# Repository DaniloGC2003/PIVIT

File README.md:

# PIVIT
Este repositório faz parte de um PIVIT, ofertado pela Universidade Tecnológica Federal do Paraná.

## Requisitos
A fim de poder rodar os programas aqui desenvolvidos, será necessário:
- Instalar a IDE do Arduino;
- Instalar dependências das placas da Espressif. Na IDE, acessar File -> Preferences. Em seguida, colar a seguinte URL em "Additional boards manager URLs":
> https://raw.githubusercontent.com/espressif/arduino-esp32/gh-pages/package_esp32_index.json

Após esse processo, as dependências necessárias para a ESP-32 usada no projeto (incluindo a biblioteca de BLE) serão instaladas.
- Instalar o boards manager da ESP32. Em Tools -> Boards -> Boards Manager, pesquisar por "esp32". Em seguida, selecionar o board ESP32S3 Dev Module.

## Topologia
A solução envolve uma rede de dispositivos que usam BLE, ESP-NOW e barramentos seriais para realizar a comunicação entre si.

Esse projeto tem como objetivo criar um teste de tempo de reação. Nele, diversos dispositivos contendo um botão e um LED serão dispostos ao alcance do usuário. Sempre que um LED é aceso, o objetivo do usuário é apertar o botão desse dispositivo o mais rápido o possível. O intervalo de tempo entre o acender do LED e a resposta do usuário é chamado de tempo de reação. Essas informações serão enviadas a um aplicativo celular.

O dispositivo mestre é a ponte de comunicação entre os dispositivos com botão e LED (chamados slaves). Ele é composto por duas ESPs: a primeira realiza transmissão de dados BLE, já a outra realiza transmissão via ESP-NOW. As ESPs do dispositivo mestre usam barramentos seriais para comunicação entre si.

Os dispositivos slaves são ESPs que se comunicam com o dispositivo mestre via ESP-NOW. Possuem a função de enviar e receber informações do dispositivo mestre e cronometrar o tempo de reação do usuário.

A interface de contato do usuário com o dispositivo master pode operar em dois modos: 
- Push button: variável operation_mode =  1. Nesse caso, a interface de contato com o usuário é apenas um push button. Mais especificamente, o dispositivo entende como interação do usuário o curto do GPIO0 com GND.
- Sensor de pressão: variável operation_mode = 0. Nesse caso, o sensor BMP280 é conectado à ESP32. O sensor medirá a pressão de uma bolsa de ar, que servirá de ponto de contato com o usuário.

Por fim, o dispositivo móvel completa a topologia da solução. O aplicativo contido nele se comunica com o mestre via BLE e é responsável por enviar ordens de ativação de slaves.

## Pasta app
Contém arquivos referentes ao aplicativo android desenvolvido. O arquivo de extensão .apk é usado para instalar o app no dispositivo móvel. O arquivo de extensão .aia é usado para realizar edições na plataforma MIT app inventor.

## Pasta ESP-NOW
Diretório que contém códigos referentes ao atual desenvolvimento da solução. A solução envolve o uso de BLE e ESP-NOW.

### master.ino
Módulo legado. Código referente ao dispositivo central da solução. Possui interface bluetooth low energy (BLE) para comunicação com o celular e interface ESP-NOW para comunicação com dispostivos slave. O dispositivo mestre age como ponte entre o usuário e os dispositivos slave.

### master_BLE_Sensor.ino
Módulo referente à interface de comunicação BLE do dispositivo mestre. Comunica-se via BLE com o celular e via UART com o mestre ESP_NOW.

### master_ESPNOW.ino
Módulo referente à interface de comunicação ESP-NOW do dispositivo mestre. Comunica-se via ESP_NOW com os dispositivos slave e via UART com o mestre BLE.

### slave.ino
Código referente aos dispositivos secundários da solução. Possui interface ESP-NOW para comunicação com o dispositivo mestre.

### utils.h
Arquivo header que contém macros e estruturas de dados usadas pelo master e pelos slaves.

### Demais pastas
Códigos auxiliares e exemplos de implementações do protocolo ESP-NOW.

## backlog.txt
Arquivo de texto contendo tarefas/implementações que devem ser discutidas no futuro.

## Pasta kicad
Contém o projeto de PCIs para os dispositivos slave.

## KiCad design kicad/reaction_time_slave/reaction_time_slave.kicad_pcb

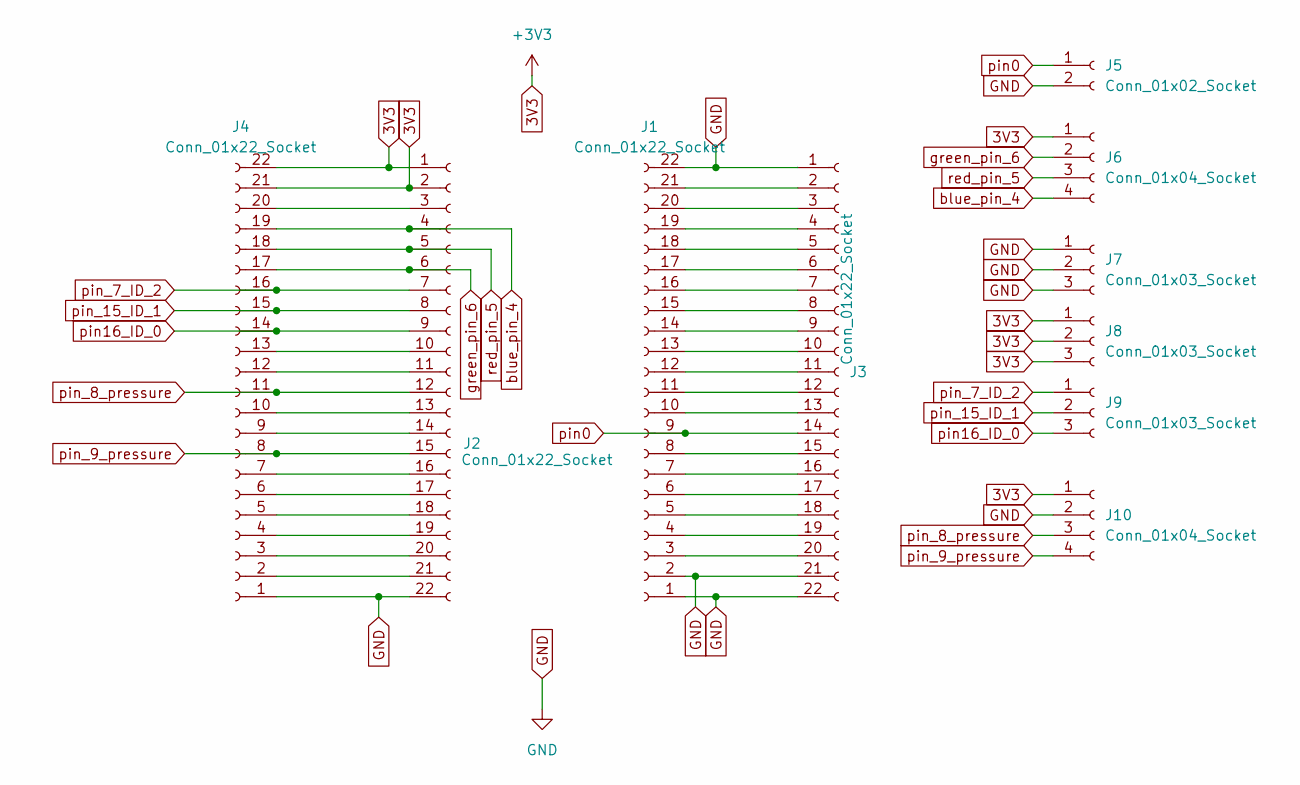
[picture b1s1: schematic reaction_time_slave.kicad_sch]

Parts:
J1, J2: Conn_01x22_Socket; PinSocket_1x22_P2.54mm_Vertical
J3, J4: Conn_01x22_Socket; PinHeader_1x22_P2.54mm_Vertical
J5: Conn_01x02_Socket; TerminalBlock_Phoenix_MKDS-1,5-2-5.08_1x02_P5.08mm_Horizont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
J6, J10: Conn_01x04_Socket; TerminalBlock_Phoenix_MKDS-1,5-4-5.08_1x04_P5.08mm_Horizont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
J7, J8, J9: Conn_01x03_Socket; PinHeader_1x03_P2.54mm_Vertical

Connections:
3V3: J2.1, J2.2, J4.21, J4.22, J6.1, J8.1, J8.2, J8.3, J10.1
GND: J1.1, J1.2, J1.22, J2.22, J3.1, J3.21, J3.22, J4.1, J5.2, J7.1, J7.2, J7.3, J10.2
unnamed: J1.3, J3.20
unnamed: J1.4, J3.19
unnamed: J1.5, J3.18
unnamed: J1.6, J3.17
unnamed: J1.7, J3.16
unnamed: J1.8, J3.15
unnamed: J1.10, J3.13
unnamed: J1.11, J3.12
unnamed: J1.12, J3.11
unnamed: J1.13, J3.10
unnamed: J1.14, J3.9
unnamed: J1.15, J3.8
unnamed: J1.16, J3.7
unnamed: J1.17, J3.6
unnamed: J1.18, J3.5
unnamed: J1.19, J3.4
unnamed: J1.20, J3.3
unnamed: J1.21, J3.2
unnamed: J2.3, J4.20
unnamed: J2.10, J4.13
unnamed: J2.11, J4.12
unnamed: J2.13, J4.10
unnamed: J2.14, J4.9
unnamed: J2.16, J4.7
unnamed: J2.17, J4.6
unnamed: J2.18, J4.5
unnamed: J2.19, J4.4
unnamed: J2.20, J4.3
unnamed: J2.21, J4.2
blue_pin_4: J2.4, J4.19, J6.4
green_pin_6: J2.6, J4.17, J6.2
pin0: J1.9, J3.14, J5.1
pin16_ID_0: J2.9, J4.14, J9.3
pin_7_ID_2: J2.7, J4.16, J9.1
pin_8_pressure: J2.12, J4.11, J10.3
pin_9_pressure: J2.15, J4.8, J10.4
pin_15_ID_1: J2.8, J4.15, J9.2
red_pin_5: J2.5, J4.18, J6.3

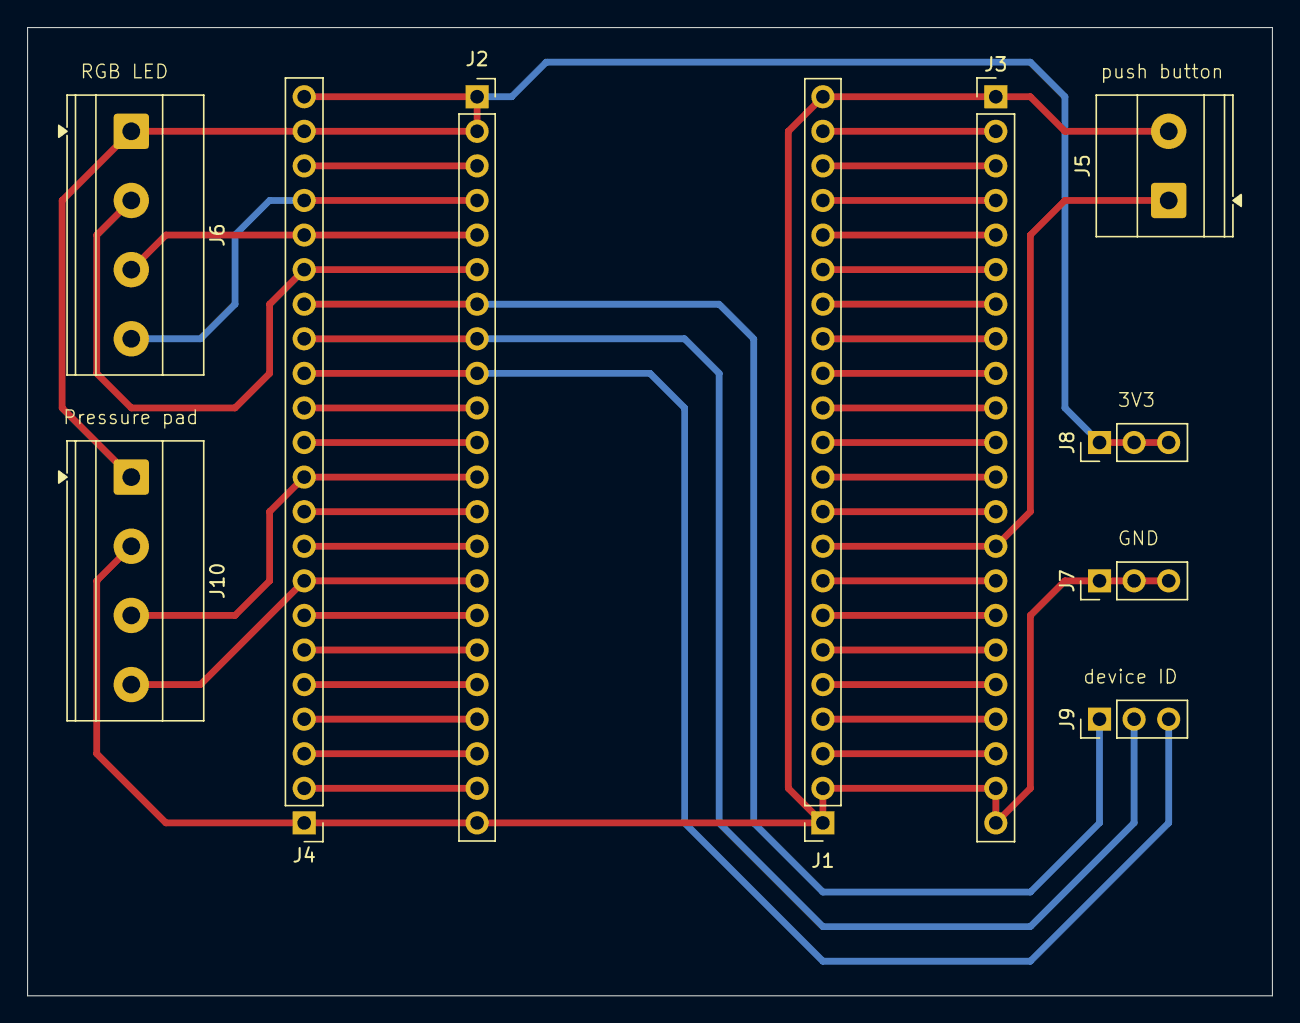
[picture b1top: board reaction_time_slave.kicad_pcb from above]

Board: 2 copper layers, 91.4 x 71.1 mm, 10 parts (0 on the bottom side), 40 nets.

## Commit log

2025-03-29 upload .ino files
2025-03-31 added notification functionality for comm. characteristic
2025-04-02 added chronometer functionality for client
2025-04-03 added known issues file; updated connection procedure for client
2025-04-07 added question
2025-04-23 added ESP-NOW files
2025-04-29 added slave device
2025-04-29 integrated master and slave
2025-04-29 - Implementação de cronômetro em slave.ino - Editado arquivo README com introdução aos arquivos do repo - Adicionado backlog.txt
2025-05-05 adicionada pergunta sobre implementação do botão
2025-05-05 Início de implementação de envio de mensagens pelo slave
2025-05-07 Adicionada sugestão em perguntas.txt
    Nova sugestão sobre interface de conexão do aplicativo.
2025-05-08 Adicionados requisitos necessários em README.md
2025-05-12 implementado payload de resposta do slave
2025-05-12 adicionada pergunta
2025-05-12 adicionada tarefa no backlog
2025-05-28 adicionados identificadores aos slaves
2025-05-29 informacoes de slave enviadas ao app
2025-06-02 started implementing buttons for all slaves
2025-06-09 adicionado novo approach no backlog
2025-06-15 added 2-device master approach
2025-06-18 established serial communication in master devices
2025-06-23 atualização dos requisitos em README.md
2025-06-24 tratamento de dado serial em master_ESPNOW.ino
2025-06-25 creating serial payload
2025-07-01 criado protocolo de envio e recebimento de dados seriais
2025-07-01 informações do slave aparecem no aplicativo
2025-07-03 implementados códigos de todos os slaves
2025-07-05 logs melhorados
2025-07-09 Update README.md
    Adicionadas descrições de novos módulos.
    Adicionada explicação da topologia.
2025-09-25 added on-board RGB LED control
2025-09-25 uploaded app's latest version
2025-09-25 uploaded .aia app file
2025-09-28 App: added automatic control
2025-10-29 PCB project
2025-11-15 updating kicad proj
2025-11-18 added PCB update
2025-11-19 changed header orientation
2026-02-23 moved sensor.ino
2026-03-24 push button and pressure pad operation modes in only one file
2026-03-25 implemented FastLED methods to master
2026-04-08 max pressure is now sent to app
2026-04-14 implemented ACK message from slave to ESP-NOW master
2026-04-17 fixed pressure pad logic
    before this fix, if the app instantly sent an activation request after receiving a reaction time from the same device, the pressure pad would get increasingly 'harder' to hit, since the reference pre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
2026-04-17 added comments, removed logs
2026-04-29 created resend attempts variable
2026-06-01 cleared backlog
2026-06-01 updated documentation
2026-06-01 added backups to .gitignore
